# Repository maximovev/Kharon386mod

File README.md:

# Kharon386mod

License CC BY-SA 4.0

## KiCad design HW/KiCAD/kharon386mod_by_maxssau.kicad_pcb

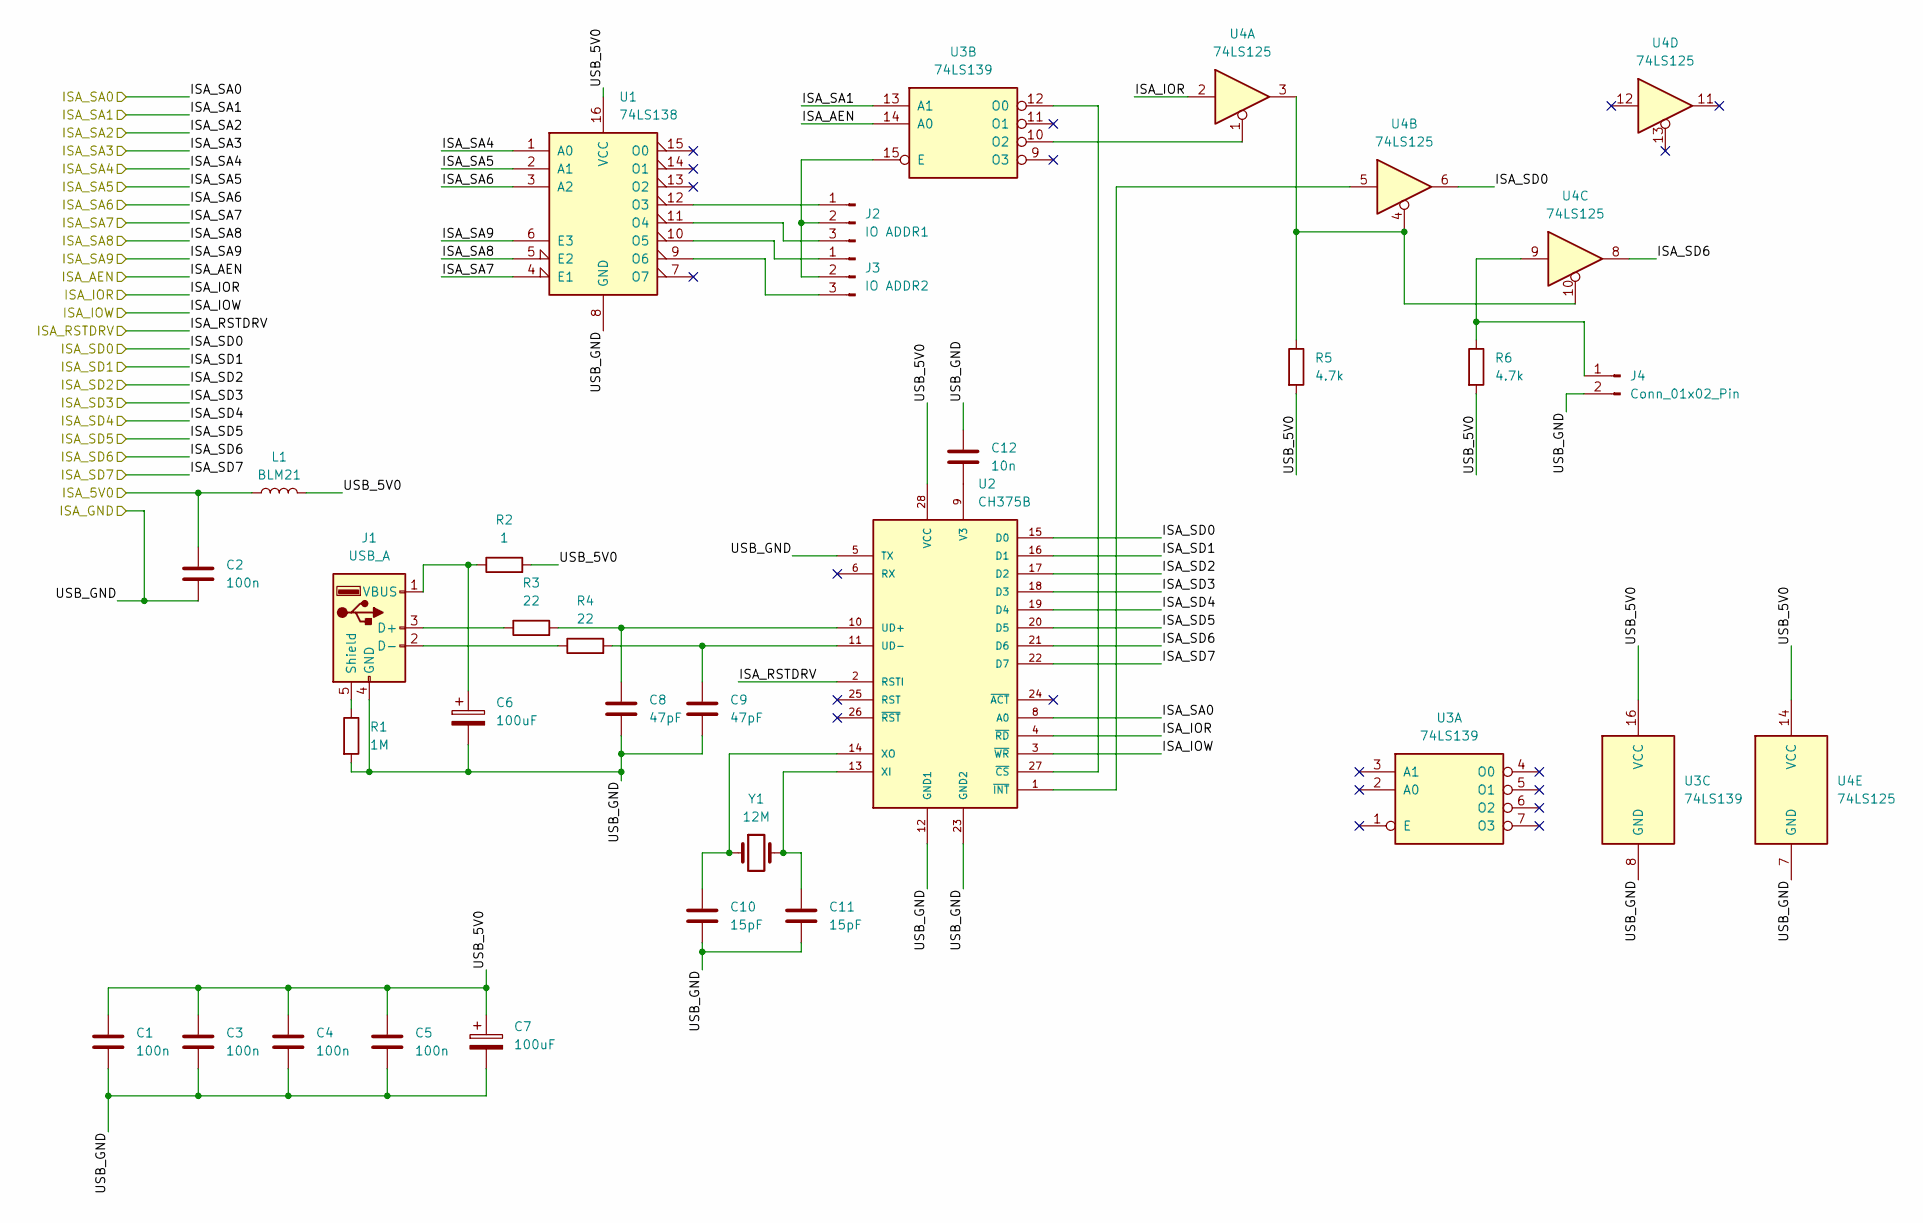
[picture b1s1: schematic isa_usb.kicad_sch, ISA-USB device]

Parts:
C1, C2, C3, C4, C5: 100n; C_0805_2012Metric_Pad1.18x1.45mm_HandSolder
C6, C7: 100uF; CP_Elec_6.3x5.9
C8, C9: 47pF; C_0805_2012Metric_Pad1.18x1.45mm_HandSolder
C10, C11: 15pF; C_0805_2012Metric_Pad1.18x1.45mm_HandSolder
C12: 10n; C_0805_2012Metric_Pad1.18x1.45mm_HandSolder
J1: USB_A; USB_A_Connfly_DS1095
J2: IO ADDR1; PinHeader_1x03_P2.54mm_Vertical
J3: IO ADDR2; PinHeader_1x03_P2.54mm_Vertical
J4: Conn_01x02_Pin; PinHeader_1x02_P2.54mm_Vertical
L1: BLM21; L_1210_3225Metric_Pad1.42x2.65mm_HandSolder
R1: 1M; R_0805_2012Metric_Pad1.20x1.40mm_HandSolder
R2: 1; R_0805_2012Metric_Pad1.20x1.40mm_HandSolder
R3, R4: 22; R_0805_2012Metric_Pad1.20x1.40mm_HandSolder
R5, R6: 4.7k; R_0805_2012Metric_Pad1.20x1.40mm_HandSolder
U1: 74LS138; SOIC-16_3.9x9.9mm_P1.27mm
U2: CH375B; SOP28-LL
U3: 74LS139; SO-16_3.9x9.9mm_P1.27mm
U4: 74LS125; SO-14_3.9x8.65mm_P1.27mm
Y1: 12M; Crystal_HC49-U_Vertical

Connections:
/B_ISA_5V0: C2.1, L1.1; also elsewhere on the board
/B_ISA_A0: U2.8 (A0); also elsewhere on the board
/B_ISA_A1: U3.13 (A1); also elsewhere on the board
/B_ISA_A4: U1.1 (A0); also elsewhere on the board
/B_ISA_A5: U1.2 (A1); also elsewhere on the board
/B_ISA_A6: U1.3 (A2); also elsewhere on the board
/B_ISA_A7: U1.4 (E1); also elsewhere on the board
/B_ISA_A8: U1.5 (E2); also elsewhere on the board
/B_ISA_A9: U1.6 (E3); also elsewhere on the board
/B_ISA_AEN: U3.14 (A0); also elsewhere on the board
/B_ISA_D0: U2.15 (D0), U4.6; also elsewhere on the board
/B_ISA_D1: U2.16 (D1); also elsewhere on the board
/B_ISA_D2: U2.17 (D2); also elsewhere on the board
/B_ISA_D3: U2.18 (D3); also elsewhere on the board
/B_ISA_D4: U2.19 (D4); also elsewhere on the board
/B_ISA_D5: U2.20 (D5); also elsewhere on the board
/B_ISA_D6: U2.21 (D6), U4.8; also elsewhere on the board
/B_ISA_D7: U2.22 (D7); also elsewhere on the board
/B_ISA_IOR: U2.4 (~RD), U4.2; also elsewhere on the board
/B_ISA_IOW: U2.3 (~WR); also elsewhere on the board
/B_ISA_RSTDRV: U2.2 (RSTI); also elsewhere on the board
/isa_usb/USB_5V0: C1.1, C3.1, C4.1, C5.1, C7.1, L1.2, R2.2, R5.2, R6.2, U1.16 (VCC), U2.28 (VCC), U3.16 (VCC), U4.14 (VCC)
GND: C1.2, C2.2, C3.2, C4.2, C5.2, C6.2, C7.2, C8.2, C9.2, C10.2, C11.2, C12.1, J1.4 (GND), J4.2, R1.2, U1.8 (GND), U2.5 (TX), U2.12 (GND1), U2.23 (GND2), U3.8 (GND), U4.7 (GND); also elsewhere on the board
unnamed: J1.3 (D+), R3.1
unnamed: J1.2 (D-), R4.1
unnamed: J1.5 (Shield), R1.1
unnamed: C6.1, J1.1 (VBUS), R2.1
unnamed: J2.1, U1.12 (O3)
unnamed: J2.2, J3.2, U3.15 (E)
unnamed: J2.3, U1.11 (O4)
unnamed: J3.1, U1.10 (O5)
unnamed: J3.3, U1.9 (O6)
unnamed: J4.1, R6.1, U4.9
unnamed: R5.1, U4.3, U4.4, U4.10
unnamed: C8.1, R3.2, U2.10 (UD+)
unnamed: C9.1, R4.2, U2.11 (UD-)
unnamed: C12.2, U2.9 (V3)
unnamed: C11.1, U2.13 (XI), Y1.2
unnamed: C10.1, U2.14 (XO), Y1.1
unnamed: U2.27 (~CS), U3.12 (O0)
unnamed: U2.1 (~INT), U4.5
unnamed: U3.10 (O2), U4.1
